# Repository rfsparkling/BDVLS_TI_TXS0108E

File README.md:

BIDIRECTIONAL VOLTAGE LEVEL SHIFTER
Based on Ti TXS0108E

http://www.ti.com/product/txs0108e
From Ti's website: 
"This 8-bit noninverting translator uses two separate configurable power-supply rails. The A port is designed to track VCCA. VCCA accepts any supply voltage from 1.2 V to 3.6 V. The B port is designed to track VCCB. VCCB accepts any supply voltage from 1.65 V to 5.5 V. This allows for low-voltage bidirectional translation between any of the 1.2-V, 1.5-V, 1.8-V, 2.5-V, 3.3-V, and 5-V voltage nodes."

Built, tested, works!

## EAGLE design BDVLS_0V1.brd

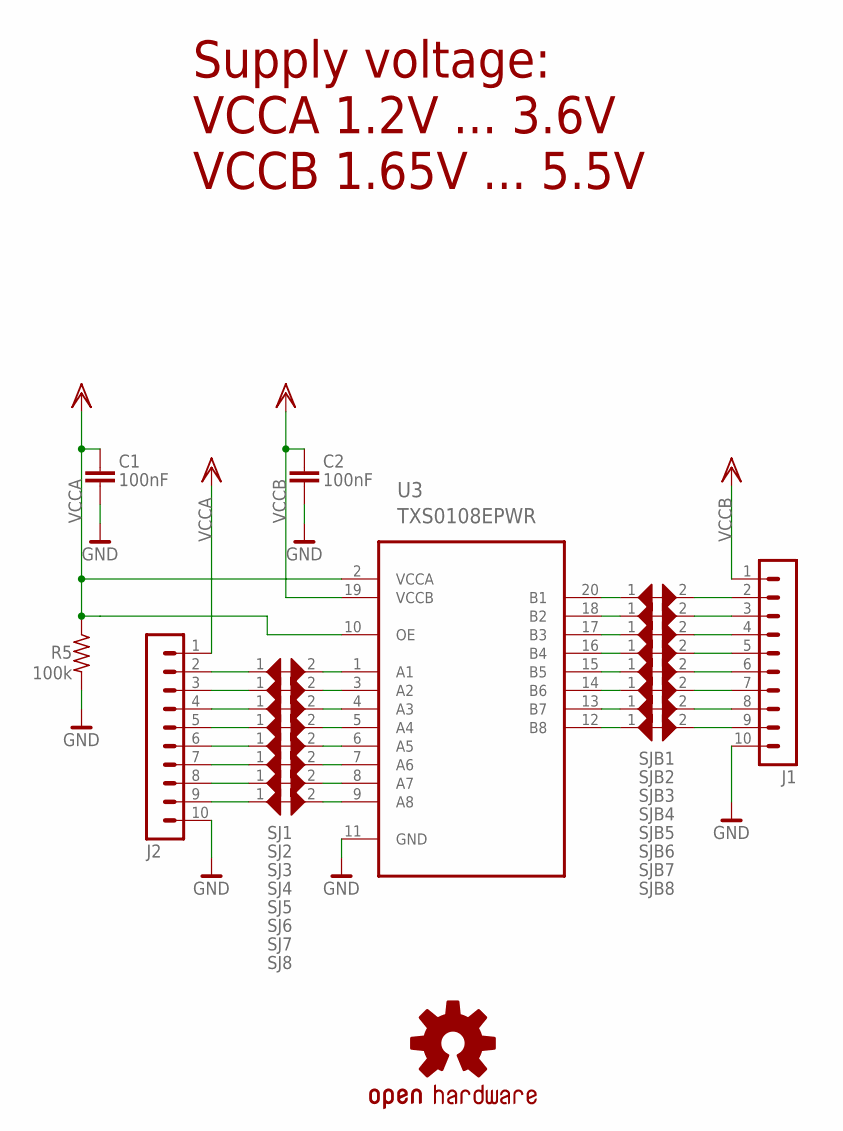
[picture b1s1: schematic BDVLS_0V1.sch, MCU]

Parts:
C1, C2: 100nF; 0603
J1, J2: PIN10S
R5: 100k; R0402
SJ1, SJ2, SJ3, SJ4, SJ5, SJ6, SJ7, SJ8: printed; JUMPER_SMD_MICRO_SHORT
SJB1, SJB2, SJB3, SJB4, SJB5, SJB6, SJB7, SJB8: printed; JUMPER_SMD_MICRO_SHORT
U3: TXS0108EPWR; SOP65P640X120-20N
U$11: OSHW-LOGOM; OSHW-LOGO-M

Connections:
A1: J2.2, SJ1.1
A2: J2.3, SJ2.1
A3: J2.4, SJ3.1
A4: J2.5, SJ4.1
A5: J2.6, SJ5.1
A6: J2.7, SJ6.1
A7: J2.8, SJ7.1
A8: J2.9, SJ8.1
B1: J1.2, SJB1.2
B2: J1.3, SJB2.2
B3: J1.4, SJB3.2
B4: J1.5, SJB4.2
B5: J1.6, SJB5.2
B6: J1.7, SJB6.2
B7: J1.8, SJB7.2
B8: J1.9, SJB8.2
GND: C1.1, C2.1, J1.10, J2.10, R5.2, U3.11 (GND)
unnamed: SJ1.2, U3.1 (A1)
unnamed: SJ2.2, U3.3 (A2)
unnamed: SJ3.2, U3.4 (A3)
unnamed: SJ4.2, U3.5 (A4)
unnamed: SJ5.2, U3.6 (A5)
unnamed: SJ6.2, U3.7 (A6)
unnamed: SJ7.2, U3.8 (A7)
unnamed: SJ8.2, U3.9 (A8)
unnamed: SJB1.1, U3.20 (B1)
unnamed: SJB2.1, U3.18 (B2)
unnamed: SJB3.1, U3.17 (B3)
unnamed: SJB4.1, U3.16 (B4)
unnamed: SJB5.1, U3.15 (B5)
unnamed: SJB6.1, U3.14 (B6)
unnamed: SJB7.1, U3.13 (B7)
unnamed: SJB8.1, U3.12 (B8)
VCCA: C1.2, J2.1, R5.1, U3.2 (VCCA), U3.10 (OE)
VCCB: C2.2, J1.1, U3.19 (VCCB)

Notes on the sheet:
Supply voltage: VCCA 1.2V ... 3.6V VCCB 1.65V ... 5.5V

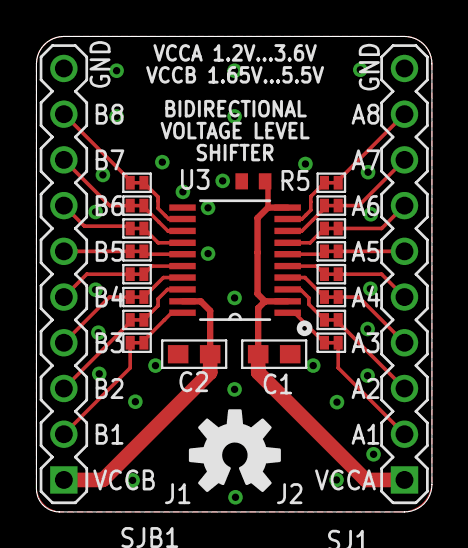
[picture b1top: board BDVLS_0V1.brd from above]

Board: 2 copper layers, 22.0 x 26.4 mm, 23 parts (0 on the bottom side), 35 nets.

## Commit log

2015-12-16 :confetti_ball: Added .gitattributes & .gitignore files
2015-12-16 adding files
2015-12-16 correction
2015-12-16 adding lic file

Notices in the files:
BDVLS_0V1.brd:
Copyright 2015
Licensed under OHL:
http://tapr.org/OHL
